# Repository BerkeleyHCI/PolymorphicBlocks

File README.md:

# Polymorphic Blocks

_subcircuit generator library based hardware description language for circuit board design_

[Try it in the browser!](https://ducky64.github.io/edg-playground/) (alpha)

Polymorphic Blocks is an open-source, Python-based [hardware description language (HDL)](https://en.wikipedia.org/wiki/Hardware_description_language) for schematic-equivalent design of printed circuit boards (PCBs).
Its library of components provide a high-level abstraction for circuit design while subcircuit generators automate the calculation of fine details.
Abstract component interfaces enable these libraries to be general across applications and component vendors.

Generates stable KiCad netlists to be routed in the KiCad PCB Editor.

### Built Boards

Many boards have been built with this system, from a mechanical keyboard macropad, to battery-powered IoT devices, to a USB source-measure unit.
Check out the [examples page](examples.md)!

## Example: from HDL to Keyboard

**Overall flow**: write HDL -> generate netlist -> import into KiCad PCB editor -> place and route (optionally iterating with HDL) -> export BoM and Gerbers -> optionally generate JLC PCBA data

A simplified version of the [getting started tutorial](getting-started.md) is this snippet for a 3x4 mechanical keyboard:

```python
from edg import *

class Keyboard(SimpleBoardTop):
    def contents(self) -> None:
        super().contents()

        self.usb = self.Block(UsbCReceptacle())
        self.reg = self.Block(LinearRegulator(3.3 * Volt(tol=0.05)))
        self.connect(self.usb.gnd, self.reg.gnd)
        self.connect(self.usb.pwr, self.reg.pwr_in)

        with self.implicit_connect(
            ImplicitConnect(self.reg.pwr_out, [Power]),
            ImplicitConnect(self.reg.gnd, [Common]),
        ) as imp:
            self.mcu = imp.Block(IoController())
            self.connect(self.usb.usb, self.mcu.usb.request())

            self.sw = self.Block(SwitchMatrix(ncols=3, nrows=4))
            self.connect(self.sw.cols, self.mcu.gpio.request_vector("sw_col"))
            self.connect(self.sw.rows, self.mcu.gpio.request_vector("sw_row"))

            self.enc = imp.Block(DigitalRotaryEncoder())
            self.connect(self.enc.a, self.mcu.gpio.request("enc_a"))
            self.connect(self.enc.b, self.mcu.gpio.request("enc_b"))
            self.connect(self.enc.with_mixin(DigitalRotaryEncoderSwitch()).sw, self.mcu.gpio.request("enc_sw"))

    def refinements(self) -> Refinements:
        return super().refinements() + Refinements(
            class_refinements=[
                (IoController, Ch32v203),
                (Switch, KailhSocket),
            ])

compile_board_inplace(Keyboard)
```

The system:
- provides a library of subcircuit generators, like switch matrices and USB-C ports, that automatically include supporting components like decoupling capacitors and pullup resistors
- automatically selects generic parts like resistors and diodes against builtin parts tables
- performs basic electrical checks on the design, including voltage and current limits, automating some common datasheet parameter checking
- runs fully locally

This generates:
- a netlist that can be imported into the KiCad PCB editor
  - ... including hierarchical data, allowing subcircuit replication / channelization
  - ... and have stable tstamps, allowing incremental updates to in-progress board layouts
- a JLCPCB-compatible BoM
  - including a [postprocessing script](edg/tools/jlc_pcba/__main__.py) to shift part rotations from KiCad-generated component placements for JLC PCBA
- a [JSON representation of the full design](edg/core/CompiledDesignExport.py), including connectivity and solved circuit values, to integrate with custom / third-party tooling

Advanced capabilities include:
- multi-board support including connector-pair management
- cross-hierarchy packing of multi-pack devices like dual op-amps and quad resistors
- standard abstract component interfaces, allowing for custom implementations of parts like resistors (including from a parts table), and microcontrollers
- full support for user component definition; very little is hard-coded into the infrastructure

## Getting Started

```
pip install edg
```

On first run, the system will automatically download a compatible Java runtime for the core compiler.

Then, work through building a mechanical keyboard (including subcircuit layout replication) in the [getting started tutorial](getting-started.md).

Also check out the [reference documentation](reference.md) for a concise list of capabilities.

Some documentation is available for library parts construction.
Be warned, this is more complex and less polished. 
See the [library block definition tutorial using KiCad schematic import](getting_started_schimport.md) and the [library construction reference](reference_library.md).

## Compared to Hierarchical Schematics

The main goal of this HDL is to enable the creation of _general_ subcircuit libraries that can be reused across many applications.

While graphical schematic tools support hierarchical sheets, direct re-use is limited because the sheets encode a lot of per-design information, like a specific resistor values or footprints.
Different users may have different requirements (e.g., different resistor values for a LED based on its input voltage, or preference for through-hole vs. surface-mount components).

This HDL addresses those limitations with two mechanisms:
- **Generators** allow the implementation of the subcircuit to depend on high-level parameters.
  A LED circuit could automatically size its resistor based on the input voltage.
- **Abstract parts** allow the subcircuit to use generic parts with generic interfaces, which many parts can implement.
  An abstract resistor interface could be implemented by through-hole and surface-mount resistors, enabling a generic LED circuit and deferring the choice.
  The top-level designer can then specify _refinements_ to make the specific choice of parts.

Both of these combined also present a higher level of abstraction for the board designer, more at the system architecture level-of-design than schematics.
We suspect this will also make it easier for novices to design boards, reducing the knowledge barrier to entry.

### Graphical Tooling

The fundamental design structure is the hierarchical block diagram, and we expect graphical tooling can layer cleanly on top of the HDL core.
Our current focus is on the HDL core and parts libraries, but we are open to collaborations with those interested in building graphical tooling.
We suspect this may be particularly useful for novice users.

We built a proof-of-concept mixed textual / graphical [IDE plugin for IntelliJ / PyCharm](https://github.com/BerkeleyHCI/edg-ide).
It has some nifty concepts (including a block diagram visualizer and [design space sweep](https://doi.org/10.1145/3613904.3642009)) but is rough around the edges and only sees basic maintenance.
It could be a good source for ideas for community developers.

## Additional Notes 

### Project Status
**This is functional has been used to [produce a wide variety of boards](examples.md) over the years.**
While the core is reasonably stable, as a pre-v1.0-release there are no formal guarantees of API stability.
In practice, deprecation shims are / will be maintained for common features if APIs change.

This started as an academic research project and continues to be developed as a personal project post-graduation, including for designing boards for fun.

### (Some) Dragons Be Ahead
Many functional boards have been built with this system and most of the library parts have been physically tested (some across many designs), but there may still be bugs and edge cases.
You are recommended to sanity check generated designs during layout.

Be prepared for things to be rough around the edges.
The error messages in particular are not great and need work.

Building boards with the included libraries should be relatively straightforward, but building custom library parts is a more complex process.

### Scope
The current libraries best support intermediate-level (and simpler) PCB designs.
This includes circuits with discrete microcontrollers, microcontroller modules (like ESP32s), and socketed dev boards.
Libraries include common subcircuits like switch matrices, digitally attached peripherals like I2C sensors, voltage converters, and some analog signal conditioning circuits.
Check out the [subcircuits library folder](edg/circuits/) and [parts library folder](edg/parts/).

There is no prescribed architecture and microcontrollers are not required.

ESPHome boards are a great fit.

Designs that do not decompose neatly(ish) into subcircuits blocks are a poor fit.

There is no support for high-speed digital design (like DDR memories).
There are some experimental RF subcircuits.

The electrical checks are not a design assurance tool and only automate some of the most common datasheet checks.
More advanced parameters, especially performance characteristics not related to maximum ratings, are currently out of scope of the electronics model.

### Parameter Engine

This system has a concept of parameters (variables, think voltages and currents) that can be attached to blocks and propagate through ports.
This is limited to directed assignments, with the goal of deterministic, predictable compilation.

Assertions are supported on parameters to enforce electrical correctness checks.

Solving may happen within a single block with arbitrary Python code (for example, find the best set of E12 resistor values to implement a divider), but not across multiple blocks.
Search involving multiple blocks must be handled by the block exposing tuning knobs and the user turning those knobs with recompilation.

### Parts Data

Most passive parts / discretes are selected from a 2022 JLCPCB parts table (included in this repository).
JLC no longer makes parts tables publicly available.

This parts table still works well and boards have been built using this table as recently as 2026.
Some basic parts have drifted and some parts may be no longer stocked.

### Contributing
We take pull requests and would love to see contributions and collaborations!

See [CONTRIBUTING.md](CONTRIBUTING.md) for details.

### Papers
This started as an academic project, though with the goal of broader adoption.
Check out our papers (all open-access), which have more details:
- [System overview, UIST'20](http://dx.doi.org/10.1145/3379337.3415860) (some details may be out of date)
- [Mixed block-diagram / textual code IDE, UIST'21](https://dl.acm.org/doi/10.1145/3472749.3474804)
- [Array ports and multi-packed devices, SCF'22](https://doi.org/10.1145/3559400.3561997)
- [Design space sweep / exploration, CHI'24](https://doi.org/10.1145/3613904.3642009)

### Misc
- **_What is EDG?_**:
  [Embedded Device Generation](https://dl.acm.org/doi/10.1145/3083157.3083159) (or more generally Electronic Device Generation) was a prior version of this project that focused on algorithms and models for embedded device synthesis, though it lacked a user-facing component.
  This project is a continuation of that work focusing on an end-to-end system, and for most of its development cycle has been called `edg`.
  But, for the purposes of writing research papers, naming collisions are confusing and bad, and we chose to keep the repo and paper name consistent.

### Generated KiCad schematic views (opt-in)

See [schematic export](docs/schematic-export.md) for generated review schematics,
symbol mappings, and validation requirements. PB Python remains the source of truth.

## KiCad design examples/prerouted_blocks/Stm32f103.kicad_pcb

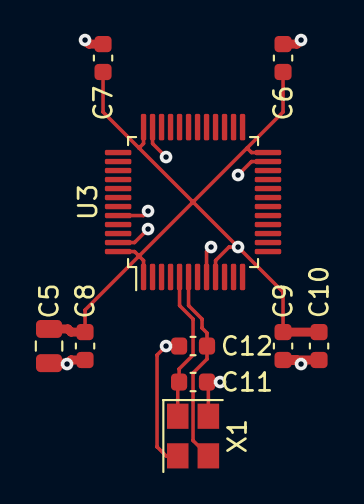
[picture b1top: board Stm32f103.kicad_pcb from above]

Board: 2 copper layers, 10 parts (0 on the bottom side), 4 nets.

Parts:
C5: C1779; C_0805_2012Metric
C6, C7, C8: C14663; C_0603_1608Metric
C9: C57112; C_0603_1608Metric
C10: C15849; C_0603_1608Metric
C11, C12: C1663; C_0603_1608Metric
U3: C8734; LQFP-48_7x7mm_P0.5mm
X1: C9002; Crystal_SMD_3225-4Pin_3.2x2.5mm

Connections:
gnd: C5.2, C6.2, C7.2, C8.2, C9.2, C10.2, C11.2, C12.2, U3.8, U3.23, U3.35, U3.44, U3.47, X1.2, X1.4
mcu.crystal.crystal.a: C11.1, U3.5, X1.1
mcu.crystal.crystal.b: C12.1, U3.6, X1.3
v3v3: C5.1, C6.1, C7.1, C8.1, C9.1, C10.1, U3.1, U3.9, U3.24, U3.36, U3.48

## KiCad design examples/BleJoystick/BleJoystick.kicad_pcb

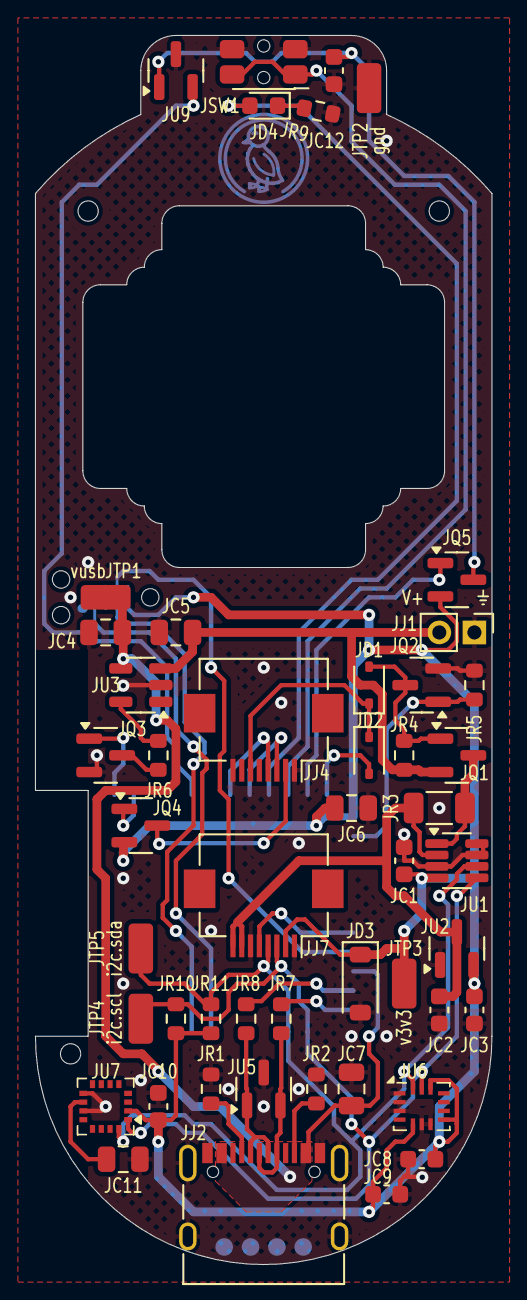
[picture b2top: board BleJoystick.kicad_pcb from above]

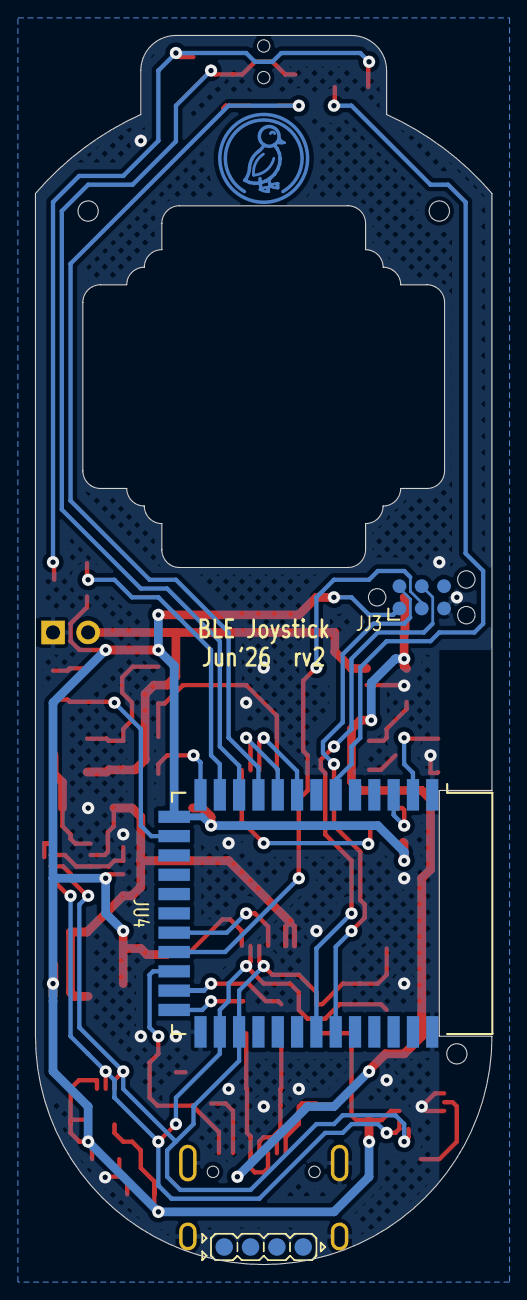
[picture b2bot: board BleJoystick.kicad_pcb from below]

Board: 2 copper layers, 26.0 x 70.0 mm, 55 parts (3 on the bottom side), 36 nets.

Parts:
JC1: vbat_sense.vs_cap; C_0603_1608Metric
JC2: reg_3v3.in_cap; C_0603_1608Metric
JC3: reg_3v3.out_cap; C_0603_1608Metric
JC4: chg.vdd_cap; C_0805_2012Metric
JC5: chg.vbat_cap; C_0805_2012Metric
JC6: mcu.vcc_cap; C_0805_2012Metric
JC7: mcu.vbus_cap; C_0805_2012Metric
JC8: imu.vdd_cap; C_0603_1608Metric
JC9: imu.vddio_cap; C_0603_1608Metric
JC10: mag.vdd_cap; C_0603_1608Metric
JC11: mag.c1; C_0805_2012Metric
JC12: trig.cbyp; C_0603_1608Metric
JD1: gate.ctl_diode; D_SOD-323
JD2: gate.btn_diode; D_SOD-323
JD3: prot_3v3; D_SOD-123
JD4: ledr.package; LED_0603_1608Metric
JH1: jlc_th.th1; JlcToolingHole_1.152mm
JH2: jlc_th.th2; JlcToolingHole_1.152mm
JH3: jlc_th.th3; JlcToolingHole_1.152mm
JJ1: bat; PinHeader_1x02_P2.00mm_Vertical
JJ2: usb.conn; USB_C_Receptacle_XKB_U262-16XN-4BVC11
JJ3: mcu.swd; Tag-Connect_TC2030-IDC-NL_2x03_P1.27mm_Vertical
JJ4: stick; Hirose_FH12-8S-0.5SH_1x08-1MP_P0.50mm_Horizontal
JJ7: btns; Hirose_FH12-8S-0.5SH_1x08-1MP_P0.50mm_Horizontal
JQ1: gate.pwr_fet; SOT-23
JQ2: gate.amp_fet; SOT-23
JQ3: chg.prog_sw; SOT-23
JQ4: stick_gate; SOT-23
JQ5: trig_gate; SOT-23
JR1: usb.cc_pull.cc1; R_0603_1608Metric
JR2: usb.cc_pull.cc2; R_0603_1608Metric
JR3: vbat_sense.Rs; R_1206_3216Metric
JR4: gate.pull_res; R_0603_1608Metric
JR5: gate.amp_res; R_0603_1608Metric
JR6: chg.prog_res; R_0603_1608Metric
JR7: mcu.usb_res.dp; R_0603_1608Metric
JR8: mcu.usb_res.dm; R_0603_1608Metric
JR9: ledr.res; R_0603_1608Metric
JR10: i2c_pull.scl_res; R_0603_1608Metric
JR11: i2c_pull.sda_res; R_0603_1608Metric
JSW1: bumper_sw; SW_SPST_EVQP7C
JTP1: vusb; TestPoint_TE_RCT_0805
JTP2: gnd; TestPoint_TE_RCT_0805
JTP3: v3v3; TestPoint_TE_RCT_0805
JTP4: i2c.scl; TestPoint_TE_RCT_0805
JTP5: i2c.sda; TestPoint_TE_RCT_0805
JU1: vbat_sense.ic; SOT-23-8
JU2: reg_3v3.ic; SOT-23
JU3: chg.ic; SOT-23-5
JU4: mcu.ic; Holyiot-18010-NRF52840
JU5: usb_esd; SOT-23
JU6: imu.ic; Bosch_LGA-14_3x2.5mm_P0.5mm
JU7: mag.ic; LGA-16_3x3mm_P0.5mm
JU9: trig.ic; SOT-23
duck: G***; Symbol_Duckling

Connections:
Jbtns.io0: JJ7.5, JU4.20
Jbumper_sw.out: JSW1.1, JU4.11
Jchg.ic.prog: JR6.2, JU3.5
Jchg.prog_ctl: JQ3.1, JU4.2
Jchg.prog_res.gnd: JQ3.3, JR6.1
Jgate.btn_in: JD1.1, JD2.1, JJ4.6
Jgate.btn_out: JD2.2, JU4.13
Jgate.control: JQ2.1, JR5.2, JU4.15
Jgate.pull_res.b: JD1.2, JQ1.1, JQ2.3, JR4.2
Jgnd: JC1.2, JC2.2, JC3.2, JC4.2, JC5.2, JC6.2, JC7.2, JC8.2, JC9.2, JC10.2, JC11.2, JC12.2, JD3.2, JJ1.1, JJ2.A1, JJ2.A12, JJ2.B1, JJ2.B12, JJ2.S1, JJ3.5, JJ4.1, JJ4.8, JJ7.1, JJ7.6, JQ2.2, JQ3.2, JR1.1, JR2.1, JR5.1, JR9.2, JSW1.2, JTP2.1, JU1.3, JU1.7, JU1.8, JU2.1, JU3.2, JU4.1, JU4.25, JU4.37, JU5.3, JU6.1, JU6.2, JU6.3, JU6.6, JU6.7, JU7.9, JU7.11, JU9.3
Jledr.package.k: JD4.1, JR9.1
Jledr.signal: JD4.2, JU4.10
Jmag.ic.c1: JC11.1, JU7.10
Jmcu.reset_node: JJ3.3, JU4.21
Jmcu.swd_node.swclk: JJ3.4, JU4.31
Jmcu.swd_node.swdio: JJ3.2, JU4.32
Jmcu.usb_res.interior.dm: JR8.2, JU4.23
Jmcu.usb_res.interior.dp: JR7.2, JU4.24
Jstick.ax1: JJ4.4, JU4.8
Jstick.ax2: JJ4.3, JU4.9
Jstick.pwr: JJ4.2, JQ4.3
Jstick_gate.control: JQ4.1, JU4.3
Jtrig.out: JU4.6, JU9.2
Jtrig.pwr: JC12.1, JQ5.3, JU9.1
Jtrig_gate.control: JQ5.1, JU4.12
Jusb.conn.cc.cc1: JJ2.A5, JR1.2
Jusb.conn.cc.cc2: JJ2.B5, JR2.2
Jusb_chain_0.d_N: JJ2.A7, JJ2.B7, JR8.1, JU5.1
Jusb_chain_0.d_P: JJ2.A6, JJ2.B6, JR7.1, JU5.2
Jv3v3: JC1.1, JC3.1, JC6.1, JC8.1, JC9.1, JC10.1, JD3.1, JJ3.1, JJ7.2, JQ4.2, JQ5.2, JR10.1, JR11.1, JTP3.1, JU1.4, JU2.2, JU4.14, JU6.5, JU6.8, JU6.12, JU7.2
Jvbat: JC5.1, JJ1.2, JQ1.2, JR4.1, JU3.3
Jvbat_gated: JC2.1, JJ7.7, JJ7.8, JR3.2, JU1.2, JU2.3
Jvbat_sense.i2c.scl: JJ7.3, JR10.2, JTP4.1, JU1.5, JU4.26, JU6.13, JU7.1
Jvbat_sense.i2c.sda: JJ7.4, JR11.2, JTP5.1, JU1.6, JU4.27, JU6.14, JU7.16
Jvbat_sense.sense_pwr_in: JQ1.3, JR3.1, JU1.1
Jvusb: JC4.1, JC7.1, JJ2.A4, JJ2.A9, JJ2.B4, JJ2.B9, JTP1.1, JU3.4, JU4.22

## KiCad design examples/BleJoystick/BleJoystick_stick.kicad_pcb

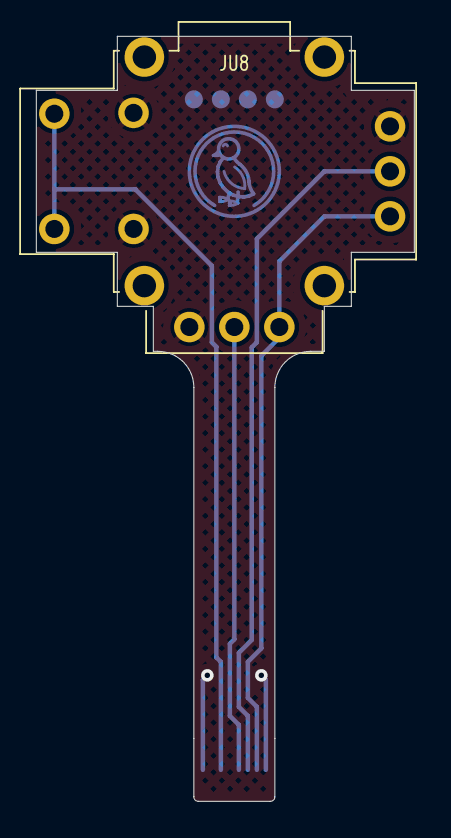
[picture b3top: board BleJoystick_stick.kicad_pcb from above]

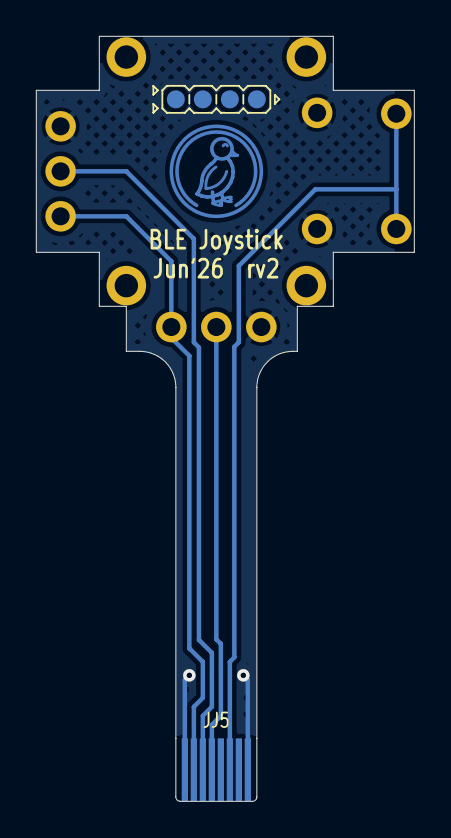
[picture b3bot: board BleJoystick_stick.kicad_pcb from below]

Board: 2 copper layers, 21.0 x 42.5 mm, 3 parts (2 on the bottom side), 5 nets.

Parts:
JJ5: stick.conn; FpcTab_1x08_P0.50mm
JU8: stick.stick; Joystick_XboxElite2
duck: G***; Symbol_Duckling

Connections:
Jstick_stick.ax1: JJ5.5, JU8.4
Jstick_stick.ax2: JJ5.6, JU8.7
Jstick_stick.gnd: JJ5.1, JJ5.8, JU8.2, JU8.3, JU8.8
Jstick_stick.pwr: JJ5.7, JU8.5, JU8.6
Jstick_stick.sw: JJ5.3, JU8.1

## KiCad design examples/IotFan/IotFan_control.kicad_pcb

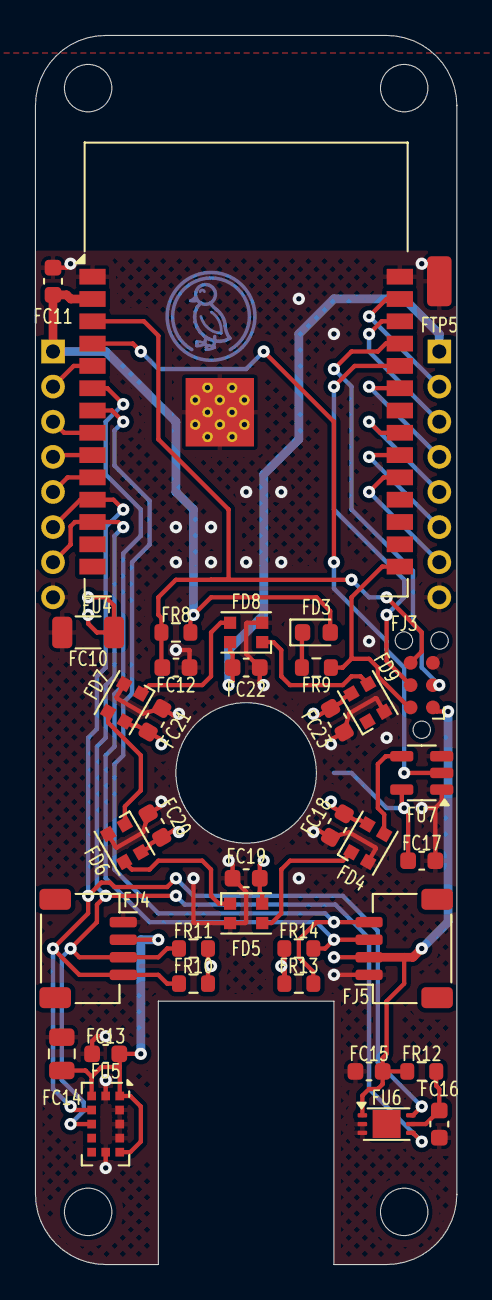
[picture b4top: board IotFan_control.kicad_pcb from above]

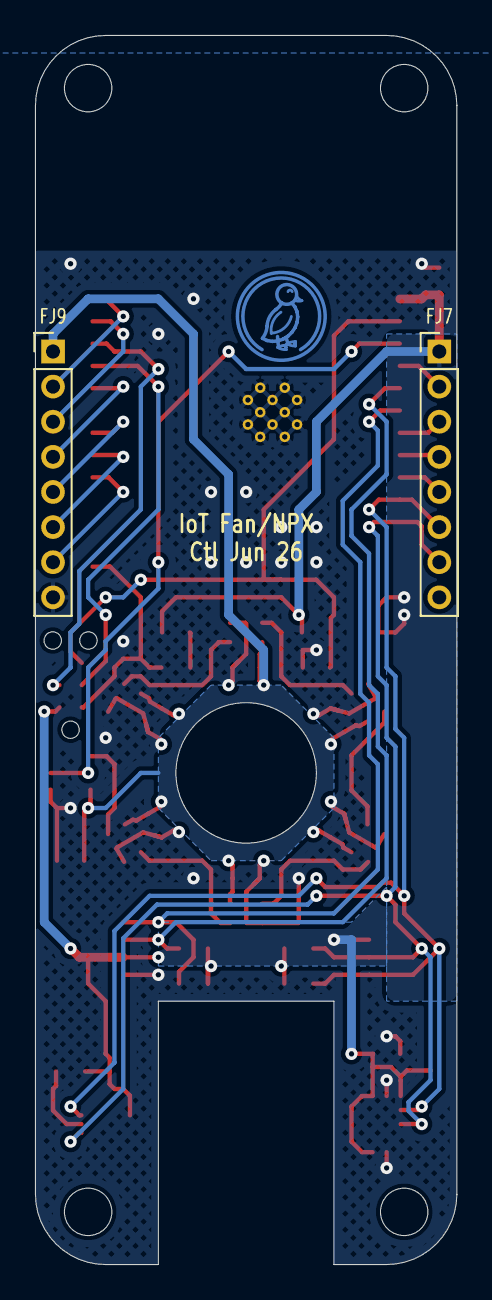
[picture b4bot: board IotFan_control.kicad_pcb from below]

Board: 2 copper layers, 24.0 x 70.0 mm, 43 parts (3 on the bottom side), 30 nets.

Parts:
FC10: control.mcu.vcc_cap0; C_1206_3216Metric
FC11: control.mcu.vcc_cap1; C_0603_1608Metric
FC12: control.mcu.en_pull.c; C_0603_1608Metric
FC13: control.dist.vdd_cap[0]; C_0603_1608Metric
FC14: control.dist.vdd_cap[1]; C_0805_2012Metric
FC15: control.als.vcc_cap; C_0603_1608Metric
FC16: control.als.dvi_pull.c; C_0603_1608Metric
FC17: control.npx_shift.vdd_cap; C_0603_1608Metric
FC18: control.npx.led[0].cap; C_0603_1608Metric
FC19: control.npx.led[1].cap; C_0603_1608Metric
FC20: control.npx.led[2].cap; C_0603_1608Metric
FC21: control.npx.led[3].cap; C_0603_1608Metric
FC22: control.npx.led[4].cap; C_0603_1608Metric
FC23: control.npx.led[5].cap; C_0603_1608Metric
FD3: control.ledr.package; LED_0603_1608Metric
FD4: control.npx.led[0].device; LED_WS2812B-2020_PLCC4_2.0x2.0mm
FD5: control.npx.led[1].device; LED_WS2812B-2020_PLCC4_2.0x2.0mm
FD6: control.npx.led[2].device; LED_WS2812B-2020_PLCC4_2.0x2.0mm
FD7: control.npx.led[3].device; LED_WS2812B-2020_PLCC4_2.0x2.0mm
FD8: control.npx.led[4].device; LED_WS2812B-2020_PLCC4_2.0x2.0mm
FD9: control.npx.led[5].device; LED_WS2812B-2020_PLCC4_2.0x2.0mm
FJ3: control.mcu.prog; Tag-Connect_TC2030-IDC-NL_2x03_P1.27mm_Vertical
FJ4: control.qwiic; JST_SH_SM04B-SRSS-TB_1x04-1MP_P1.00mm_Horizontal
FJ5: control.qwiic2; JST_SH_SM04B-SRSS-TB_1x04-1MP_P1.00mm_Horizontal
FJ7: control.conn1; PinHeader_1x08_P2.00mm_Vertical
FJ9: control.conn2; PinHeader_1x08_P2.00mm_Vertical
FR8: control.mcu.en_pull.r; R_0603_1608Metric
FR9: control.ledr.res; R_0603_1608Metric
FR10: control.i2c_pull.scl_res; R_0603_1608Metric
FR11: control.i2c_pull.sda_res; R_0603_1608Metric
FR12: control.als.dvi_pull.r; R_0603_1608Metric
FR13: control.i2c2_pull.scl_res; R_0603_1608Metric
FR14: control.i2c2_pull.sda_res; R_0603_1608Metric
FTP5: gnd; TestPoint_TE_RCT_0805
FU4: control.mcu.ic; ESP32-S3-WROOM-1
FU5: control.dist.ic; ST_VL53L0X
FU6: control.als.ic; HVSOF6
FU7: control.npx_shift.ic; SOT-23-5
H1, H2, H3, H4: MountingHole_2.7mm_M2.5_ISO14580
duck: G***; Symbol_Duckling

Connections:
Fcontrol_control.als.ic.dvi: FC16.1, FR12.2, FU6.5
Fcontrol_control.drv: FJ9.3, FU4.38
Fcontrol_control.enc_a: FJ9.5, FU4.33
Fcontrol_control.enc_b: FJ9.6, FU4.32
Fcontrol_control.enc_sw: FJ9.7, FU4.31
Fcontrol_control.extra1: FJ9.4, FU4.35
Fcontrol_control.gnd: FC10.2, FC11.2, FC12.2, FC13.2, FC14.2, FC15.2, FC16.2, FC17.2, FC18.2, FC19.2, FC20.2, FC21.2, FC22.2, FC23.2, FD4.2, FD5.2, FD6.2, FD7.2, FD8.2, FD9.2, FJ3.5, FJ4.1, FJ5.1, FJ7.8, FJ9.8, FTP5.1, FU4.1, FU4.40, FU4.41, FU5.2, FU5.3, FU5.4, FU5.6, FU5.12, FU6.2, FU6.3, FU7.1, FU7.3
Fcontrol_control.i2c2_pull.i2c.scl: FJ5.4, FR13.2, FU4.7
Fcontrol_control.i2c2_pull.i2c.sda: FJ5.3, FR14.2, FU4.6
Fcontrol_control.i2c.scl: FJ4.4, FJ7.6, FR10.2, FU4.11, FU5.10, FU6.6
Fcontrol_control.i2c.sda: FJ4.3, FJ7.7, FR11.2, FU4.12, FU5.9, FU6.4
Fcontrol_control.ledr.package.k: FD3.1, FR9.1
Fcontrol_control.mcu.program_boot_node: FJ3.2, FR9.2, FU4.27
Fcontrol_control.mcu.program_en_node: FC12.1, FJ3.6, FR8.2, FU4.3
Fcontrol_control.mcu.program_uart_node.a_tx: FJ3.4, FU4.36
Fcontrol_control.mcu.program_uart_node.b_tx: FJ3.3, FU4.37
Fcontrol_control.npx.led[0].dout: FD4.1, FD5.3
Fcontrol_control.npx.led[1].dout: FD5.1, FD6.3
Fcontrol_control.npx.led[2].dout: FD6.1, FD7.3
Fcontrol_control.npx.led[3].dout: FD7.1, FD8.3
Fcontrol_control.npx.led[4].dout: FD8.1, FD9.3
Fcontrol_control.npx_en: FJ7.2, FU4.5
Fcontrol_control.npx_shift.input: FU4.4, FU7.2
Fcontrol_control.npx_shift.output: FD4.3, FU7.4
Fcontrol_control.pd_int: FJ7.5, FU4.10
Fcontrol_control.pwm: FJ7.3, FU4.8
Fcontrol_control.spk: FJ7.4, FU4.9
Fcontrol_control.tach: FJ9.2, FU4.39
Fcontrol_control.v3v3: FC10.1, FC11.1, FC13.1, FC14.1, FC15.1, FD3.2, FJ3.1, FJ4.2, FJ5.2, FJ7.1, FR8.1, FR10.1, FR11.1, FR12.1, FR13.1, FR14.1, FU4.2, FU5.1, FU5.5, FU5.11, FU6.1
Fcontrol_control.v5: FC17.1, FC18.1, FC19.1, FC20.1, FC21.1, FC22.1, FC23.1, FD4.4, FD5.4, FD6.4, FD7.4, FD8.4, FD9.4, FJ9.1, FU7.5

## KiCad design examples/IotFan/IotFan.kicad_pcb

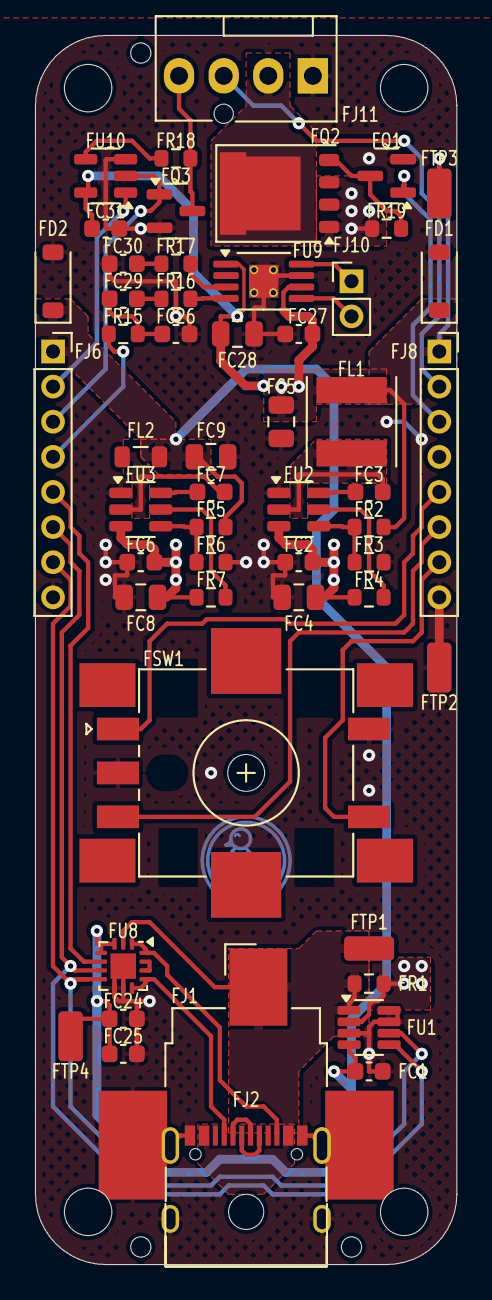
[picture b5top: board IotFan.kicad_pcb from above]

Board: 2 copper layers, 24.0 x 70.0 mm, 61 parts (1 on the bottom side), 40 nets.

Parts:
FC1: vin_sense.vs_cap; C_0603_1608Metric
FC2: reg_5v.hf_in_cap; C_0603_1608Metric
FC3: reg_5v.boot_cap; C_0603_1608Metric
FC4: reg_5v.power_path.in_cap; C_0805_2012Metric
FC5: reg_5v.power_path.out_cap; C_0805_2012Metric
FC6: reg_3v3.hf_in_cap; C_0603_1608Metric
FC7: reg_3v3.boot_cap; C_0603_1608Metric
FC8: reg_3v3.power_path.in_cap; C_0805_2012Metric
FC9: reg_3v3.power_path.out_cap; C_0805_2012Metric
FC24: pd.vdd_cap[0]; C_0603_1608Metric
FC25: pd.vdd_cap[1]; C_0603_1608Metric
FC26: spk_dac.c; C_0603_1608Metric
FC27: spk_drv.pwr_cap; C_0603_1608Metric
FC28: spk_drv.bulk_cap; C_0805_2012Metric
FC29: spk_drv.inp_cap; C_0603_1608Metric
FC30: spk_drv.inn_cap; C_0603_1608Metric
FC31: npx_shift.vdd_cap; C_0603_1608Metric
FD1: prot_5v; D_SOD-123
FD2: prot_3v3; D_SOD-123
FH1: jlc_th.th1; JlcToolingHole_1.152mm
FH2: jlc_th.th2; JlcToolingHole_1.152mm
FH3: jlc_th.th3; JlcToolingHole_1.152mm
FJ1: pwr; BarrelJack_CUI_PJ-036AH-SMT_Horizontal
FJ2: usb; USB_C_Receptacle_XKB_U262-16XN-4BVC11
FJ6: control.conn1; PinSocket_1x08_P2.00mm_Vertical
FJ8: control.conn2; PinSocket_1x08_P2.00mm_Vertical
FJ10: spk; PinHeader_1x02_P2.00mm_Vertical
FJ11: fan; FanPinHeader_1x04_P2.54mm_Vertical
FL1: reg_5v.power_path.inductor; L_Taiyo-Yuden_NR-50xx
FL2: reg_3v3.power_path.inductor; L_0805_2012Metric
FQ1: fan_drv.pre; SOT-23
FQ2: fan_drv.drv; PQFN-8-EP_6x5mm_P1.27mm_Generic
FQ3: fan_ctl; SOT-23
FR1: vin_sense.Rs; R_0603_1608Metric
FR2: reg_5v.fb.top_res; R_0603_1608Metric
FR3: reg_5v.fb.bottom_res; R_0603_1608Metric
FR4: reg_5v.en_res; R_0603_1608Metric
FR5: reg_3v3.fb.top_res; R_0603_1608Metric
FR6: reg_3v3.fb.bottom_res; R_0603_1608Metric
FR7: reg_3v3.en_res; R_0603_1608Metric
FR15: spk_dac.r; R_0603_1608Metric
FR16: spk_drv.inp_res; R_0603_1608Metric
FR17: spk_drv.inn_res; R_0603_1608Metric
FR18: npx_res; R_0603_1608Metric
FR19: fan_drv.pull; R_0603_1608Metric
FSW1: enc; RotaryEncoder_Alps_EC11J15-Switch
FTP1: _pwr_merge_pwr_out_link; TestPoint_TE_RCT_0805
FTP2: gnd; TestPoint_TE_RCT_0805
FTP3: v5; TestPoint_TE_RCT_0805
FTP4: v3v3; TestPoint_TE_RCT_0805
FU1: vin_sense.ic; SOT-23-8
FU2: reg_5v.ic; SOT-23-6
FU3: reg_3v3.ic; SOT-23-6
FU8: pd.ic; WQFN-14-1EP_2.5x2.5mm_P0.5mm_EP1.45x1.45mm
FU9: spk_drv.ic; MSOP-8-1EP_3x3mm_P0.65mm_EP1.68x1.88mm_ThermalVias
FU10: npx_shift.ic; SOT-23-5
H1, H2, H3, H4: MountingHole_2.7mm_M2.5_ISO14580
UU4: Duck; Symbol_Duckling

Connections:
Fcontrol.drv: FJ8.3, FQ1.1
Fcontrol.enc_a: FJ8.5, FSW1.A
Fcontrol.enc_b: FJ8.6, FSW1.B
Fcontrol.enc_sw: FJ8.7, FSW1.S1
Fcontrol.npx_en: FJ6.2, FU10.1
Fcontrol.pd_int: FJ6.5, FU8.5
Fcontrol.pwm: FJ6.3, FQ3.1, FU10.2
Fcontrol.spk: FJ6.4, FR15.1
Fcontrol.tach: FJ8.2, FJ11.3
Ffan.pwr: FJ11.2, FQ2.5
Ffan_drv.pre.drain: FQ1.3, FQ2.4, FR19.2
Fgnd: FC1.2, FC2.2, FC4.2, FC5.2, FC6.2, FC8.2, FC9.2, FC24.2, FC25.2, FC26.2, FC27.2, FC28.2, FC30.2, FC31.2, FD1.2, FD2.2, FJ1.2, FJ2.A1, FJ2.A12, FJ2.B1, FJ2.B12, FJ2.S1, FJ6.8, FJ8.8, FJ11.1, FQ1.2, FQ3.2, FR3.2, FR6.2, FSW1.C, FSW1.S2, FTP2.1, FU1.3, FU1.7, FU1.8, FU2.1, FU3.1, FU8.8, FU8.9, FU8.15, FU9.7, FU9.9, FU10.3
Fnpx_res.output: FJ11.4, FQ3.3, FR18.2
Fnpx_shift.output: FR18.1, FU10.4
Fpd.ic.vconn: FU8.12, FU8.13
Fpwr.pwr: FJ1.1, FJ2.A4, FJ2.A9, FJ2.B4, FJ2.B9, FR1.1, FTP1.1, FU1.1, FU8.2
Freg_3v3.ic.boot: FC7.1, FU3.6
Freg_3v3.ic.en: FR7.2, FU3.5
Freg_3v3.ic.fb: FR5.2, FR6.1, FU3.4
Freg_3v3.ic.sw: FC7.2, FL2.1, FU3.2
Freg_5v.ic.boot: FC3.1, FU2.6
Freg_5v.ic.en: FR4.2, FU2.5
Freg_5v.ic.fb: FR2.2, FR3.1, FU2.4
Freg_5v.ic.sw: FC3.2, FL1.1, FU2.2
Fspk_dac.output: FC26.1, FC29.2, FR15.2
Fspk_drv.ic.inn: FR17.2, FU9.3
Fspk_drv.ic.inp: FR16.2, FU9.4
Fspk_drv.inn_res.input: FC30.1, FR17.1
Fspk_drv.inp_res.input: FC29.1, FR16.1
Fspk_drv.spk.a: FJ10.1, FU9.8
Fspk_drv.spk.b: FJ10.2, FU9.5
Fusb.cc.cc1: FJ2.A5, FU8.10, FU8.11
Fusb.cc.cc2: FJ2.B5, FU8.1, FU8.14
Fusb.usb.dm: FJ2.A7, FJ2.B7
Fusb.usb.dp: FJ2.A6, FJ2.B6
Fv3v3: FC1.1, FC9.1, FC24.1, FC25.1, FD2.1, FJ6.1, FL2.2, FR5.1, FTP4.1, FU1.4, FU8.3, FU8.4
Fv5: FC5.1, FC6.1, FC8.1, FC27.1, FC28.1, FC31.1, FD1.1, FJ8.1, FL1.2, FR2.1, FR7.1, FTP3.1, FU3.3, FU9.1, FU9.6, FU10.5
Fvin: FC2.1, FC4.1, FQ2.1, FQ2.2, FQ2.3, FR1.2, FR4.1, FR19.1, FU1.2, FU2.3
Fvin_sense.i2c.scl: FJ6.6, FU1.5, FU8.6
Fvin_sense.i2c.sda: FJ6.7, FU1.6, FU8.7

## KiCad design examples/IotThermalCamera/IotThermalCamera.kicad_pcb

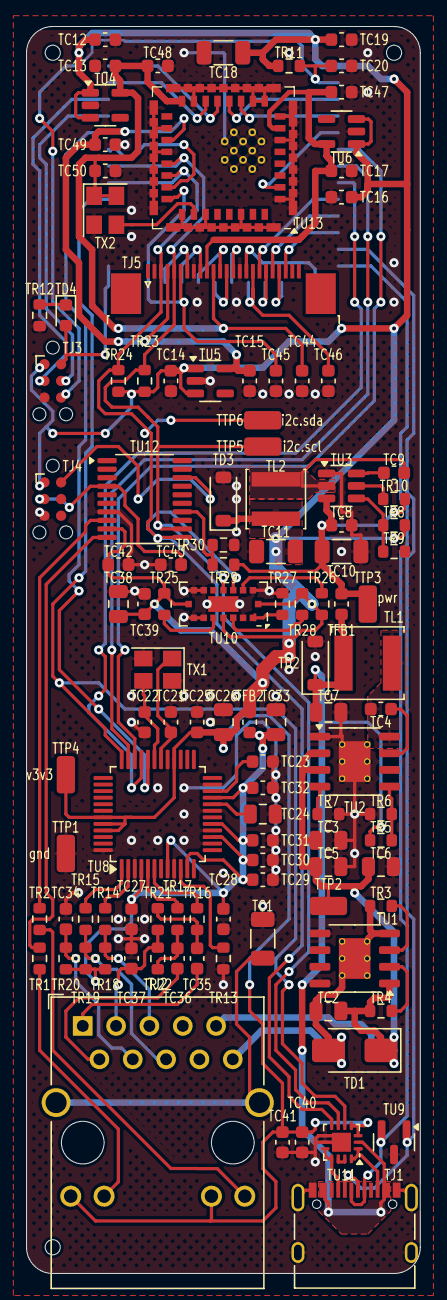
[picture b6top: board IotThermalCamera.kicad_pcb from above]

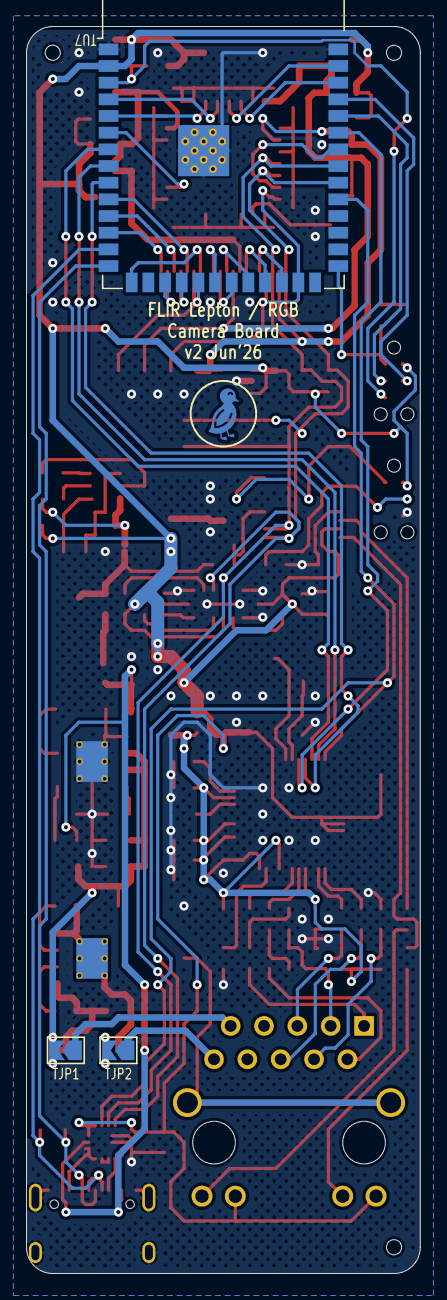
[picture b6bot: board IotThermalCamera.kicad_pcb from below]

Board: 2 copper layers, 30.0 x 95.0 mm, 120 parts (4 on the bottom side), 88 nets.

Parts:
TC1: eth.cap; C_1206_3216Metric
TC2: poe.vdd_cap; C_0805_2012Metric
TC3: reg_poe.hf_cap; C_0805_2012Metric
TC4: reg_poe.boot_cap; C_0603_1608Metric
TC5: reg_poe.power_path.in_cap.c[0]; C_0805_2012Metric
TC6: reg_poe.power_path.in_cap.c[1]; C_0805_2012Metric
TC7: reg_poe.power_path.out_cap; C_0805_2012Metric
TC8: reg_3v3.hf_in_cap; C_0603_1608Metric
TC9: reg_3v3.boot_cap; C_0603_1608Metric
TC10: reg_3v3.power_path.in_cap; C_1206_3216Metric
TC11: reg_3v3.power_path.out_cap; C_1206_3216Metric
TC12: reg_3v0.in_cap; C_0603_1608Metric
TC13: reg_3v0.out_cap; C_0603_1608Metric
TC14: reg_2v8.in_cap; C_0603_1608Metric
TC15: reg_2v8.out_cap; C_0603_1608Metric
TC16: reg_1v2.in_cap; C_0603_1608Metric
TC17: reg_1v2.out_cap; C_0603_1608Metric
TC18: mcu.vcc_cap0; C_1206_3216Metric
TC19: mcu.vcc_cap1; C_0603_1608Metric
TC20: mcu.en_pull.c; C_0603_1608Metric
TC21: phy.crystal.cap_a; C_0603_1608Metric
TC22: phy.crystal.cap_b; C_0603_1608Metric
TC23: phy.c1v20; C_0603_1608Metric
TC24: phy.tocap; C_0805_2012Metric
TC25: phy.vdd_cap0; C_0603_1608Metric
TC26: phy.vdd_cap1; C_0805_2012Metric
TC27: phy.avdd_caps[0]; C_0603_1608Metric
TC28: phy.avdd_caps[1]; C_0603_1608Metric
TC29: phy.avdd_caps[2]; C_0603_1608Metric
TC30: phy.avdd_caps[3]; C_0603_1608Metric
TC31: phy.avdd_caps[4]; C_0603_1608Metric
TC32: phy.avdd_caps[5]; C_0603_1608Metric
TC33: phy.avdd_caps[6]; C_0805_2012Metric
TC34: phy.txc_cap; C_0603_1608Metric
TC35: phy.rxp_ac; C_0603_1608Metric
TC36: phy.rxn_ac; C_0603_1608Metric
TC37: phy.rxc_cap; C_0603_1608Metric
TC38: dist.avdd_cap; C_0805_2012Metric
TC39: dist.iovdd_cap; C_0603_1608Metric
TC40: pd.vdd_cap[0]; C_0603_1608Metric
TC41: pd.vdd_cap[1]; C_0603_1608Metric
TC42: ioe.vdd_cap; C_0603_1608Metric
TC43: ioe.reset_cap; C_0603_1608Metric
TC44: cam.dovdd_cap; C_0603_1608Metric
TC45: cam.reset_cap; C_0603_1608Metric
TC46: cam.pclk_cap; C_0603_1608Metric
TC47: flir.vddc_cap; C_0603_1608Metric
TC48: flir.vddio_cap; C_0603_1608Metric
TC49: flir.vdd_cap; C_0603_1608Metric
TC50: flir.mclk.cap; C_0603_1608Metric
TD1: poe.prot; D_SMA
TD2: prot_v5; D_SOD-123
TD3: prot_3v3; D_SOD-123
TD4: ledr.package; LED_0603_1608Metric
TFB1: choke; L_0603_1608Metric
TFB2: phy.l; L_0603_1608Metric
TH1: jlc_th.th1; JlcToolingHole_1.152mm
TH2: jlc_th.th2; JlcToolingHole_1.152mm
TH3: jlc_th.th3; JlcToolingHole_1.152mm
TJ1: usb; USB_C_Receptacle_XKB_U262-16XN-4BVC11
TJ2: eth.conn; RJ45_Wuerth_7499111446_Horizontal
TJ3: mcu.prog; Tag-Connect_TC2030-IDC-NL_2x03_P1.27mm_Vertical
TJ4: ioe.sdi; Tag-Connect_TC2030-IDC-NL_2x03_P1.27mm_Vertical
TJ5: cam.device; TE_2-1734839-4_1x24-1MP_P0.5mm_Horizontal
TJP1: poe_jmp.pos; SolderJumper-2_P1.3mm_Open_TrianglePad1.0x1.5mm
TJP2: poe_jmp.neg; SolderJumper-2_P1.3mm_Open_TrianglePad1.0x1.5mm
TL1: reg_poe.power_path.inductor; L_Sunlord_SWPA5040S
TL2: reg_3v3.power_path.inductor; L_Sunlord_SWPA4030S
TR1: eth.led_yel_res; R_0603_1608Metric
TR2: eth.led_grn_res; R_0603_1608Metric
TR3: poe.cls; R_0603_1608Metric
TR4: poe.den; R_0603_1608Metric
TR5: reg_poe.fb.top_res; R_0603_1608Metric
TR6: reg_poe.fb.bottom_res; R_0603_1608Metric
TR7: reg_poe.rt; R_0603_1608Metric
TR8: reg_3v3.fb.top_res; R_0603_1608Metric
TR9: reg_3v3.fb.bottom_res; R_0603_1608Metric
TR10: reg_3v3.en_res; R_0603_1608Metric
TR11: mcu.en_pull.r; R_0603_1608Metric
TR12: ledr.res; R_0603_1608Metric
TR13: phy.exres1; R_0603_1608Metric
TR14: phy.txp_damp; R_0603_1608Metric
TR15: phy.txn_damp; R_0603_1608Metric
TR16: phy.rxp_damp; R_0603_1608Metric
TR17: phy.rxn_damp; R_0603_1608Metric
TR18: phy.txp_bias; R_0603_1608Metric
TR19: phy.txn_bias; R_0603_1608Metric
TR20: phy.txc_bias; R_0603_1608Metric
TR21: phy.rxp_bias; R_0603_1608Metric
TR22: phy.rxn_bias; R_0603_1608Metric
TR23: i2c_pull.scl_res; R_0603_1608Metric
TR24: i2c_pull.sda_res; R_0603_1608Metric
TR25: dist.lpn_pull; R_0603_1608Metric
TR26: dist.rsvd6_pull; R_0603_1608Metric
TR27: dist.i2c_rst_pull; R_0603_1608Metric
TR28: dist.int_pull; R_0603_1608Metric
TR29: poe_sense.top_res; R_0603_1608Metric
TR30: poe_sense.bottom_res; R_0603_1608Metric
TTP1: gnd; TestPoint_TE_RCT_0805
TTP2: _poe_pwr_out_link; TestPoint_TE_RCT_0805
TTP3: pwr; TestPoint_TE_RCT_0805
TTP4: v3v3; TestPoint_TE_RCT_0805
TTP5: i2c.scl; TestPoint_TE_RCT_0805
TTP6: i2c.sda; TestPoint_TE_RCT_0805
TU1: poe.ic; HSOP-8-1EP_3.9x4.9mm_P1.27mm_EP2.41x3.1mm_ThermalVias
TU2: reg_poe.ic; HSOP-8-1EP_3.9x4.9mm_P1.27mm_EP2.41x3.1mm_ThermalVias
TU3: reg_3v3.ic; SOT-23-6
TU4: reg_3v0.ic; SOT-23-5
TU5: reg_2v8.ic; SOT-23-5
TU6: reg_1v2.ic; SOT-23-5
TU7: Symbol_DucklingSolid
TU7#2: mcu.ic; ESP32-S3-WROOM-1
TU8: phy.ic; LQFP-48_7x7mm_P0.5mm
TU9: usb_esd; SOT-23
TU10: dist.ic; ST_VL53L5x
TU11: pd.ic; WQFN-14-1EP_2.5x2.5mm_P0.5mm_EP1.45x1.45mm
TU12: ioe.ic; TSSOP-20_4.4x6.5mm_P0.65mm
TU13: flir.ic; Molex_1050281001
TX1: phy.crystal.package; Crystal_SMD_3225-4Pin_3.2x2.5mm
TX2: flir.mclk.device; Crystal_SMD_3225-4Pin_3.2x2.5mm

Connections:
Tcam.dvp8.href: TJ5.9, TU7#2.23
Tcam.dvp8.pclk: TC46.1, TJ5.17, TU7#2.19
Tcam.dvp8.vsync: TJ5.7, TU7#2.24
Tcam.dvp8.xclk: TJ5.13, TU7#2.21
Tcam.dvp8.y0: TJ5.19, TU7#2.18
Tcam.dvp8.y1: TJ5.21, TU7#2.17
Tcam.dvp8.y2: TJ5.22, TU7#2.12
Tcam.dvp8.y3: TJ5.20, TU7#2.11
Tcam.dvp8.y4: TJ5.18, TU7#2.10
Tcam.dvp8.y5: TJ5.16, TU7#2.15
Tcam.dvp8.y6: TJ5.14, TU7#2.20
Tcam.dvp8.y7: TJ5.12, TU7#2.22
Tcam.reset: TC45.1, TJ5.6, TU7#2.25, TU13.24
Tdist.ic.i2c_rst: TR27.2, TU10.A1
Tdist.ic.int: TR28.2, TU10.A3
Tdist.ic.lpn: TR25.2, TU10.A5
Tdist.ic.rsvd6: TR26.2, TU10.C2
Teth.conn.led_grn_cathode: TJ2.14, TR2.1
Teth.conn.led_yel_cathode: TJ2.12, TR1.1
Teth.conn.shield: TC1.1, TJ2.SH
Teth.eth.rx.center: TC37.1, TJ2.3, TR21.2, TR22.2
Teth.eth.rx.neg: TC36.1, TJ2.2
Teth.eth.rx.pos: TC35.1, TJ2.1
Teth.eth.tx.center: TC34.1, TJ2.4, TR20.2
Teth.eth.tx.neg: TJ2.6, TR15.2, TR19.2
Teth.eth.tx.pos: TJ2.5, TR14.2, TR18.2
Teth.led_grn_sink: TR2.2, TU12.8
Teth.led_yel_sink: TR1.2, TU12.10
Teth.poe.neg: TJ2.10, TJP2.1
Teth.poe.pos: TJ2.9, TJP1.1
Tflir.cs: TU7#2.38, TU13.14
Tflir.ic.master_clk: TU13.26, TX2.3
Tflir.shutdown: TU7#2.34, TU13.23
Tflir.spi.miso: TU7#2.4, TU13.12
Tflir.spi.mosi: TU7#2.5, TU13.11
Tflir.spi.sck: TU7#2.39, TU13.13
Tflir.vsync: TU7#2.6, TU13.2
Tgnd: TC1.2, TC3.2, TC5.2, TC6.2, TC7.2, TC8.2, TC10.2, TC11.2, TC12.2, TC13.2, TC14.2, TC15.2, TC16.2, TC17.2, TC18.2, TC19.2, TC20.2, TC21.2, TC22.2, TC23.2, TC24.2, TC25.2, TC26.2, TC27.2, TC28.2, TC29.2, TC30.2, TC31.2, TC32.2, TC33.2, TC34.2, TC37.2, TC38.2, TC39.2, TC40.2, TC41.2, TC42.2, TC43.2, TC44.2, TC45.2, TC46.2, TC47.2, TC48.2, TC49.2, TC50.2, TD2.2, TD3.2, TJ1.A1, TJ1.A12, TJ1.B1, TJ1.B12, TJ1.S1, TJ3.5, TJ4.5, TJ5.2, TJ5.8, TJ5.15, TR6.2, TR7.1, TR9.2, TR12.2, TR13.1, TR27.1, TR30.2, TTP1.1, TU1.5, TU1.8, TU2.1, TU2.9, TU3.1, TU4.2, TU5.2, TU6.2, TU7#2.1, TU7#2.40, TU7#2.41, TU8.3, TU8.9, TU8.14, TU8.16, TU8.19, TU8.23, TU8.29, TU8.48, TU9.3, TU10.A2, TU10.A6, TU10.A7, TU10.B4, TU10.C1, TU10.C6, TU10.C7, TU11.8, TU11.9, TU11.15, TU12.7, TU13.1, TU13.6, TU13.8, TU13.9, TU13.10, TU13.15, TU13.18, TU13.20, TU13.25, TU13.27, TU13.30, TU13.33, TX1.2, TX1.4, TX2.2
Ti2c_chain_0.scl: TJ5.5, TR23.2, TTP5.1, TU7#2.33, TU10.C4, TU11.6, TU12.12, TU13.21
Ti2c_chain_0.sda: TJ5.3, TR24.2, TTP6.1, TU7#2.32, TU10.C3, TU11.7, TU12.11, TU13.22
Tioe.ic.nrst: TC43.1, TJ4.3, TU12.4
Tioe.ic.swio: TJ4.2, TU12.18
Tledr.package.k: TD4.1, TR12.1
Tmcu.program_boot_node: TD4.2, TJ3.2, TU7#2.27
Tmcu.program_en_node: TC20.1, TJ3.6, TR11.2, TU7#2.3
Tmcu.program_uart_node.a_tx: TJ3.4, TU7#2.36
Tmcu.program_uart_node.b_tx: TJ3.3, TU7#2.37
Tpd.ic.vconn: TU11.12, TU11.13
Tphy.cs: TU7#2.35, TU8.32
Tphy.ic.avdd: TC27.1, TC28.1, TC29.1, TC30.1, TC31.1, TC32.1, TC33.1, TFB2.2, TR18.1, TR19.1, TR20.1, TU8.4, TU8.8, TU8.11, TU8.15, TU8.17, TU8.21
Tphy.ic.crystal.xtal_in: TC21.1, TU8.30, TX1.1
Tphy.ic.crystal.xtal_out: TC22.1, TU8.31, TX1.3
Tphy.ic.exres1: TR13.2, TU8.10
Tphy.ic.rxn: TR17.1, TU8.5
Tphy.ic.rxp: TR16.1, TU8.6
Tphy.ic.tocap: TC24.1, TU8.20
Tphy.ic.txn: TR15.1, TU8.1
Tphy.ic.txp: TR14.1, TU8.2
Tphy.ic.v1v20: TC23.1, TU8.22
Tphy.int: TU7#2.31, TU8.36, TU11.5
Tphy.rxn_damp.b: TC36.2, TR17.2, TR22.1
Tphy.rxp_damp.b: TC35.2, TR16.2, TR21.1
Tphy.spi.miso: TU7#2.7, TU8.34
Tphy.spi.mosi: TU7#2.8, TU8.35
Tphy.spi.sck: TU7#2.9, TU8.33
Tpoe.ic.cls: TR3.2, TU1.3
Tpoe.ic.den: TR4.2, TU1.2
Tpoe.poe.neg: TC2.2, TD1.2, TJP2.2, TR3.1, TU1.4, TU1.9
Tpoe.pwr_out: TC2.1, TC3.1, TC5.1, TC6.1, TD1.1, TJP1.2, TR4.1, TTP2.1, TU1.1, TU2.2, TU2.3
Tpoe_sense.output: TR29.2, TR30.1, TU12.14
Tpwr: TC8.1, TC10.1, TFB1.2, TR10.1, TR29.1, TTP3.1, TU3.3
Treg_3v3.ic.boot: TC9.1, TU3.6
Treg_3v3.ic.en: TR10.2, TU3.5
Treg_3v3.ic.fb: TR8.2, TR9.1, TU3.4
Treg_3v3.ic.sw: TC9.2, TL2.1, TU3.2
Treg_poe.ic.boot: TC4.1, TU2.7
Treg_poe.ic.fb: TR5.2, TR6.1, TU2.5
Treg_poe.ic.rt: TR7.2, TU2.4
Treg_poe.ic.sw: TC4.2, TL1.1, TU2.8
Tusb.cc.cc1: TJ1.A5, TU11.10, TU11.11
Tusb.cc.cc2: TJ1.B5, TU11.1, TU11.14
Tusb.pwr: TC7.1, TD2.1, TFB1.1, TJ1.A4, TJ1.A9, TJ1.B4, TJ1.B9, TL1.2, TR5.1, TU11.2
Tusb_chain_0.d_N: TJ1.A7, TJ1.B7, TU7#2.13, TU9.1
Tusb_chain_0.d_P: TJ1.A6, TJ1.B6, TU7#2.14, TU9.2
Tv1v2: TC17.1, TC47.1, TJ5.10, TU6.5, TU13.7
Tv2v8: TC15.1, TC49.1, TJ5.4, TU5.5, TU13.19
Tv3v0: TC13.1, TC44.1, TC48.1, TC50.1, TJ5.11, TU4.5, TU13.16, TX2.1, TX2.4
Tv3v3: TC11.1, TC12.1, TC14.1, TC16.1, TC18.1, TC19.1, TC25.1, TC26.1, TC38.1, TC39.1, TC40.1, TC41.1, TC42.1, TD3.1, TFB2.1, TJ2.11, TJ2.13, TJ3.1, TJ4.1, TL2.2, TR8.1, TR11.1, TR23.1, TR24.1, TR25.1, TR26.1, TR28.1, TTP4.1, TU4.1, TU4.3, TU5.1, TU5.3, TU6.1, TU6.3, TU7#2.2, TU8.28, TU8.43, TU8.44, TU8.45, TU10.A4, TU10.B1, TU10.B7, TU11.3, TU11.4, TU12.9
